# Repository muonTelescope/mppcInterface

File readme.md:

[headerIMG]

# MPPC Interface
Measuring and logging photon level light sources is a large part of high energy physics instrumentaiton. This board was created to power and collect data from eight MPPC (Multi Pixel photon counters) or SiPM (Silicon Photomultiplers). Provide coincidence logic and log the data out to a Raspberry Pi.

[img]

This is the main conntroller board of the muon telescope project. This board aimts to replace the current tools used

This is the technical manual for anyone wanting to modify, hack, remix, or program their own SiPM readout. The manual goes into fine detail about construction, assembly, and firmware which should encompass all basic knowledge.

## TOC

## Design
THe design was based off a combiniation of topologies from [sPhenix] design, our previous hardware iterations, and new needs in this version. The MPPCs need a very stable high voltage bias voltage that can be controled over this range in sub-milivolt steps. 

[topologyDiagarm]

This is done thoug hthe top high voltage being controalbe in 1V steps and is common across all eight chanels and a eight channel bottom DAC that provides a controlable virtual ground seperately for each channel.

The anode signal is then sent though a high amplification instrumentation amplifier and then sent to the FPGA's schmitt inputs. The conicidence logic is then done in the FPGA and its outputs are mapped to interupt vectors on the host machine.

### Components
Component selection was built off previous verisons, and the specific use case  of driving [Hamamtsu]'s MPPCs. The major ICs and other unique componets will be descibed below.

#### High Voltage Boost
*Maxim Semiconducr's* [MAX1932] has proven itself with proper layout in pervious interations of the design to provide a stable, controlable, low ripple high voltage for avalanche photodidoes. 

THe chip interanlly has a boost controller, current sensing for a current limit, and a 8b DAC that can be tied in to set the voltage over SPI.

#### Bottom DAC
The other half of the bias voltage is handled by the *Texas Instument* [DAC60508] 8 channel 12b (with a direct drop in replace for up to 16b) digital to analog converter. The linear regulation inside provides a stable output, and using the internal `2.5 V` precsion refrence LSB steps of `0.6 mV` are achived. THe output is highly linear and monotonic. 

The power consuption is also low at `0.6mA/ch` for future power constrained applicaitons.

### Schematic
### Layout
### Mechanics

## Firmware
### High Voltage
### Bottom DAC
### FPGA burning
### Compiling
### Flashing

## Gateware
### Pin connections
### Logic
### Compiling
### Flashing

## Setup
Download and flash a copy of the [Raspberry Pi OS](https://www.raspberrypi.com/software/) using either `dd` or the *Raspberry Pi imager* software.

### Raspberry Pi imager
Select the Raspberry Pi OS Lite and in advanced configuration menu (CTRL+SHIFT+X) enable ssh and add the WiFi credentials if the device will be connected over wireless network.

This video also shows using the software to flash a SD card [How to use Raspberry Pi Imager](https://www.youtube.com/watch?v=ntaXWS8Lk34)

### Advanced install with `dd`
Be very careful using `dd` to copy the image to the SD card. `dd` is a direct bit copy from the imput file to the output file and will indescriminately write over any drives without any checks or protection.

```bash
df -h
sudo umount sdx
sudo dd bs=4M if=<imgPath.img> of=/dev/sdx
```

Enable ssh by creating a blank `ssh` file in the root directory called *boot*.
```bash
cd boot
touch ssh
```

To setup connectingto WiFi on boot, a `/boot/wpa_supplicant.conf` file is created that is automatically copied over to `/etc/wpa_supplicant/wpa_supplicant.conf` on the next boot. 

```bash
nano /boot/wpa_supplicant.conf
```

And add in the relevant configuration.

```
ctrl_interface=DIR=/var/run/wpa_supplicant GROUP=netdev
country=<Insert 2 letter ISO 3166-1 country code here>
update_config=1

network={
 ssid="<Name of your wireless LAN>"
 psk="<Password for your wireless LAN>"
}
```

Insert the SD card into the Raspberry Pi, connect the ethernet cable (if connecting over wired network), and power (unless connecting though POE) and connect to the device using ssh.

You can figure out the IP address in several ways on linux you can use `nmap` or `arp` to search for the Raspberry Pi foundation's OUID (`DC:A6:32` for Raspberry Pi 4, `B8:27:EB` otherwise) on your local subnet. 

```bash
nmap -sP 192.168.1.0/24 | awk '/^Nmap/{ip=$NF}/B8:27:EB/{print ip}'
```

```bash
arp -na | grep -i b8:27:eb
```

For Windows
```cmd
arp -a | findstr b8-27-eb
```

It is also possible to ping a new install with the default hostname if DNS or the bonjour service has the device in its tables.

```bash
ping raspi
```

### Bootstrap
The setup script in the root directory can be run to set up a Raspberry pi from scratch. 

Connect to the raspberry pi using the IP adress found.
```bash
ssh pi@192.168.1.*
sudo apt install -y git
```

```bash
git clone https://github.com/muonTelescope/mppcInterface.git
cd mppcInterface
```

The root directory includes a setup script that updates the operationg system, sets up accounts, installs the toolchain, and enables all required modules. On cloning th repository on the Raspberry Pi, this file shoud be made executable and run.

```bash
chmod +x setup.sh
sudo ./setup.sh
```

expand filwsystem, not needed as pi does it on boot now.

Working buildsystem for gateware
```
Yosys 0.9+3981 (git sha1 7d2097b0, clang 7.0.1-8+rpi3+deb10u2 -fPIC -Os)
arachne-pnr 0.1+328+0 (git sha1 c40fb22, g++ 8.3.0-6+rpi1 -O2)

```

By default the spidev driver on raspberry pi has a maximum transfer size of 4096 bytes.
That might cause problems with this software so to change the default buffersize add spidev.bufsiz=65536 to /boot/cmdline.txt and reboot.
Where 65536 is the maximum size you want to allow.

get mac adress to set hostname
```bash
cat /sys/class/net/eth0/address | cut -d: -f4- | sed 's/://g' | tr [:lower:] [:upper:]
```

channelSelect.sh
```bash
#!/bin/bash

dtparam spi=off

gpio mode 6  out  # CS_DAC
gpio mode 23 out  # CS_MAX1932
gpio mode 5  out  # CS_FPGA

gpio write 6  1
gpio write 23 1
gpio write 5  1

sleep 2

gpio mode 12 out # MOSI
gpio mode 13 out # MISO
gpio mode 14 out # SCK

gpio write 12 $1
gpio write 13 $2
gpio write 14 $3

sleep 2
#rmmod spi_bcm2835
#modprobe spi_bcm2835

dtparam spi=on
```

softwareSerial read python
```python
import sys
import time
import difflib
import pigpio
import datetime
import binascii

RX=17

try:
        pi = pigpio.pi()
        pi.set_mode(RX, pigpio.INPUT)
        pi.bb_serial_read_open(RX, 115200, 8)

        print "DATA - SOFTWARE SERIAL:"
        while 1:
                (count, data) = pi.bb_serial_read(RX)
                if count:
			print str(datetime.datetime.now()) + " " +  str(binascii.hexlify(data))
                time.sleep(0.5)

except Exception as e:
	print(e)
        pi.bb_serial_read_close(RX)
        pi.stop()
```

A controller board for 

This is a continuation of a long process, over five years at this point. It is also part of a much broader set of tools and parts that make up the Muon Telesecope.

## Design

## Hardware
There are three main sections to the hardware. High voltage generation and control, Analog front end, and digital logic conatined in the FPGA.

### Bias Voltage
The MPPCs requre a bias of around 80V (varies greatly by model) with very low ripple and high precision. The gain of the sensors varies with respect to the voltage put across them and even a deviation of 10mV has a significat impact on the gain. The gain is also a function of ambient temperature and the bias needs to be controlabe to within a mV to adjust the gain as temperature changes.

[Gain vs Bias]
[Gain Vs temp chart]

The bias voltage is set though a top high voltage rail and a bottom DAC. This approach allows for a very high precision on the bottom dac along with the range on the top HV. With a 16b DAC, steps of under 100uV are possible, whcih is below the accuracy of most of the rest of the supply

For example to set the voltage to 78.434 the top rail is set to its minimal on voltage to ensure there is never a risk of a forward bias (although with the HV off the output is at 4.5V, the input voltage save the shotky didode drop so the risk is only there if the dac is ser to near its max voltage which may still be below the conduction voltage of the MPPC), then the bottom rail can be set to 1.566V, followed by the HV rail being set to 80V providing a voltage diffreential of 78.434 across the sensor.

#### HV Rail
The top high voltage rail is created using Maxim's [MAX1932] APD bias boost converter. This IC provides a low ripple 5V input to 55V to 110V output (design configurable to 20V-100V) with 8b digital control over SPI and built in current limiting set at 2.5mA.

Using a high amount of filtering on the inputs and outpurs, large bulk capacitors, a tight layout, EMC shields, and sectioned off ground and power planes, the output ripple as well as emitted noise is reduced significantly. The output ripple is well below 1mV.

The voltage range, and step size is dictated with setting R2, R3, and R4. The minimum and maximum voltage set using the equations for on page 7 of the datasheet, and there are 8 bits (256) intermediate values that are possible. The high switching portion was designed with general SMPS design requirements (short high current loops, separated ground planes, EMI shielding) providing a low ripple output (<5mVpp ripple) and no significant back EMF.

The Setting resistors are 0.01% and the chip provides a 0.5% accuracy which needs to be calibrated. The calibration and certification procedure is provided in another section of documention.

[Table of set R values and the range they create]
[Fucntion of byte to voltage with perfect resistors]

#### Bottom DAC

The "Bottom DAC" is the term used to describe the arrangement where the voltage supply at the anode of a reverse biased SiPM is used to "subtract" from the top bias voltage. It is implemented with a eight channel 16b [DAC80508] by Texas Instruments. This provides independent control with a 5V range for each of the eight chanels. 

### Analog Front End
The analog front end amplifier is also highly specilized. The design condierations to be considered are considerable and require specilized parts [MPPC AFE talk]. In the end the selection is a very high bandwidth low noise instrumentation amplifier with a 400x gain. The [OPA846] has a high slew rate of 625V/us and a gain bandwith product of 1.75Ghz providing a adequate bandwith of ~4.3Mhz with our gain. 

[Outfput waveform]

This provides waveforms from over xx photons to reach the 1.4V lower schmitt threadhold of the digital logic 3.3V/2-100mV. 

[Photn and gain calculation]
x photons needed * 40% efficency * 	1.7E6 * 1.602E-19C / nS?	

The aplifier's input in coupled with a DC blocking capacitor and routed very tightly on a single layer to reduce noise and emissions that will easily be amplified with such a high gain. The gain of 400x is acivhed with a 20k and 50R positive feedback in a non-inverting configuration. The output is AC coupled to make sure the output has minimal capacitive loading especially since we are only looking for a hihg speed signal output.

[Routing of AFE]

#### Digital Logic
The digital logic is done with a FPGA and can be reconfigured though gateware based on the detector configuration. The eight channels are connected to the GPIO and the schmitt inputs act as discriminators. The rest of the lines are run to three LEDs that can be used for indication and to the GPIO of the Raspberry Pi.

#### Power supply
The general supply rails are provide dby the host Raspberry pi connector. The entire board uses about 1W across all the modules. The 5V supply, after some back EMF filtering is provided to the HV supply as well as the AFE power module. The 3.3V is used on the FPGA and the signaling Power supply of the DAC.

Very stable +-5V rails are required for the analog front end to have have the low noise it needs. The Analog \pm 5V is seperated to its own power planes and is hevily filtered and decoupled ensuring very little noise that would show amplifed on the output. This supply is generated thougha commerical module which is rated at a low ripple and switching frequency.

A 1.2V linear regulator provides the core voltage to the FPGA.

#### Mounting
The hat is attached to the raspberry pi with four 2.6mm mounting holes form M2.5 screwas nad standoffs. A M2.5x11 standoff provides mounting and clearence. The size of the module is showin in the drawing below, it is the same sizing as a raspberry pi zero.

## Firmware
This repository contains firmware in the form of C++ libraries that can be linked into your own code as well as a basic data logging application that sets up everything and logs the counts to a file. 

#### High Voltage
The SPI bus is connected directly to the MAX1932. Chip select is active low and data is sent MSB (most significant bit first). Sending bytes to it sets the voltage. Setting them to 0x00 turns off the DC-DC converter portion. As values increase to 0xFF (256), the output voltage falls linearly.

```Arduino
//Example Arduino code that loops through all voltages.
//SCLK --> Pin 13 for Uno or Duemilanove
//DIN ---> Pin 11 for Uno or Duemilanove

#include <SPI.h>
#define CS 2 //Any pin

void setup(){
	Serial.begin(9600);
	pinMode(CS, OUTPUT);
	digitalWrite(CS, HIGH);
	SPI.begin();
	SPI.setBitOrder(MSBFIRST);
}

void loop(){
	for(int i = 0 ; i < 256 ; i++){
		digitalWrite(CS, LOW);
		SPI.transfer(i);
		digitalWrite(CS, HIGH);
		Serial.println(i);
	}
}
```

---
In the config file the voltage is set for 25*. 

#### DAC

## Gateware

#### Flashing

##### Clearing
##### Burning
##### File format

##### Compilation
###### Yosys
###### AracnePNR

## Absolute Maximum ratings
## Gaurenteed Ratings
## Manufacturing
### BOM
### PCB Assembly
The board has three fiducials and 1.152mm tooling holes for automated assembly.
### Artwork
### Labeling
## Safety
## Certifications
## Licence
## Attributions

- HV Calibration procedure and certification.

Glossary
MPPC Multi pixel photon counter, Hamamtsu Photonics's 
SiPM
DAC
Bias

# Old Version of docs

A single assembled board breaks out singals and provides all the interfaces that 4 [MPPC Sesnor](https://github.com/Sawaiz/mppcSensor) boards need. The power to each module is supplied via the [MPPC high voltage](https://github.com/Sawaiz/mppcHighVoltage) modules
attached board. It is able to be run independently for testing and debugging, or on a backplane with many others for more channels.

![][mppcInterfaceAssembly]

## Expansion Format

### SPI
The SPI exapansion format is designed to be infinetly expandable up to the signal propgation length and capactive loading. 

The Design of the SPI system is chained shift registers. The shift registers 

SPI EEPROM lies on each expansion board and has the code needed to interface with it (this sounds beautiful, really).
The EEPROM contains the device enumeration and drivers for all the 8 slots on its adress.
Master downloads drivers 

### I2C

## Hardware
The board attaches directly to a Raspberry Pi using the centered GPIO headers. The Raspberry Pi is mounted to the board via four standoffs. It is a stand alone board requiring no backplane. This board can be mounted via the M5 screw holes around the edge.

### Power
Power is supplied through two pins on the edge connector, or via the micro USB port on board. There is a 600mA buck regulator that provides power when the USB port is used. The board should be powered by 3.3V and a negative power supply module with convert it to -3.3V for the biasing for the op-amps.

### High Voltage
High voltage is supplied through a daughter board. Each channel has a independent voltage source that can be temperature modulated and monitored via the on board ADC. for more information about the modules, read [here](https://github.com/Sawaiz/mppcHighVoltage).

![][mppcInterfaceTopISO]

### Microcontroller
The side of the board has a Arduino compatible ([ATmega328](http://www.atmel.com/images/Atmel-8271-8-bit-AVR-Microcontroller-ATmega48A-48PA-88A-88PA-168A-168PA-328-328P_datasheet_Complete.pdf)) microcontroller, along with a USB part, USB to UART converter and other supporting circuitry. The button is connected to the reset pin. The programing port on board is a Tag-Connect 6 pin, and is only used for programing the Arduino bootloader.

![][mppcInterfaceBottom]

### I2C Switch
As all the ADC modules on the daughter boards have the same address, a 8 channel I2C switch ([TCA9548A](http://www.ti.com/lit/ds/symlink/tca9548a.pdf)) is used to communicate to them independently. The pins attached to it are referenced as master, as the microcontroller is acting as the master controlling it.

## BOM
The bill of materials is availible in [bom.csv](bom.csv) and is copied into a table below.

| Ref Des                                                                                          | Qty | Manufacturer          | MPN                 | Description                      |
| ------------------------------------------------------------------------------------------------ | ---:| --------------------- | ------------------- | -------------------------------- |
| C1                                                                                               | 1   | Wuerth Elektronik     | 885012105011        | CAP CER 0.22UF 10V X5R 0402      |
| C2                                                                                               | 1   | Wuerth Elektronik     | 885012208116        | CAP CER 0.047UF 100V X7R 1206    |
| C3 C5 C7 C9 C11 C13 C15 C17                                                                      | 8   | Wuerth Elektronik     | 885012205016        | CAP CER 0.047UF 10V X7R 0402     |
| C19                                                                                              | 1   | Samsung               | CL21B105KOFNNNG     | CAP CER 1UF 16V X7R 0805         |
| C20                                                                                              | 1   | Samsung               | CL31B105KCHNNNE     | CAP CER 1UF 100V X7R 1206        |
| C21                                                                                              | 1   | AVX                   | 22201C106MAT2A      | CAP CER 10UF 100V X7R 2220       |
| C22 C24                                                                                          | 2   | Murata                | GRM155C80J106ME11D  | CAP CER 10UF 6.3V X6S 0402       |
| C29 C28 C34 C33 C39 C38 C44 C43 C49 C48 C54 C53 C59 C58 C64 C63                                  | 16  | Wuerth Elektronik     | 885012105016        | CAP CER 0.1UF 16V X5R 0402       |
| C23 C32 C31 C27 C26 C37 C41 C42 C36 C4 C25 C6 C30 C8 C35 C10 C40 C12 C45 C14 C50 C16 C55 C18 C60 | 25  | Samsung               | CL05A105MP5NNNC     | CAP CER 1UF 10V X5R 0402         |
| C65                                                                                              | 1   | TDK                   | C1005X5R1A335M050BC | CAP CER 3.3UF 10V X5R 0402       |
| R1                                                                                               | 1   | Stackpole Electronics | RMCF0402FT1M13      | RES 1.13M OHM 1% 1/16W 0402      |
| R2                                                                                               | 1   | Stackpole Electronics | RMCF0402JT20R0      | RES 20 OHM 5% 1/16W 0402         |
| R3                                                                                               | 1   | Yageo                 | RT0402BRD072K49L    | RES SMD 2.49KOHM 0.1% 1/16W 0402 |
| R4                                                                                               | 1   | Yageo                 | RC0402FR-07806RL    | RES SMD 806 OHM 1% 1/16W 0402    |
| R5                                                                                               | 1   | Yageo                 | RT0402BRD07100KL    | RES SMD 100K OHM 0.1% 1/16W 0402 |
| R6                                                                                               | 1   | TE Connectivity       | CPF0402B23R7E1      | RES SMD 23.7 OHM 0.1% 1/16W 0402 |
| R7 R12 R17 R22 R27 R32 R37 R42                                                                   | 8   | Yageo                 | RT0402DRE071KL      | RES SMD 1K OHM 0.5% 1/16W 0402   |
| R8 R9 R13 R14 R18 R19 R23 R24 R28 R29 R33 R34 R38 R39 R43 R44                                    | 16  | Panasonic             | ERJ-2RKD49R9X       | RES SMD 49.9 OHM 0.5% 1/16W 0402 |
| R10 R15 R20 R25 R30 R35 R40 R45                                                                  | 8   | Stackpole Electronics | RNCF0402DTE20K0     | RES 20K OHM 0.5% 1/16W 0402      |
| R11                                                                                              | 1   | Stackpole Electronics | RMCF0402FT499K      | RES 499K OHM 1% 1/16W 0402       |
| D2                                                                                               | 1   | ON Semiconductor      | FDLL4148            | DIODE GEN PURP 100V 200MA LL34   |
| J1 J2 J3 J4 J5 J6 J7 J8                                                                          | 8   | Hirose                | U.FL-R-SMT-1(40)    | CONN U.FL RCPT STR 50 OHM SMD    |
| J9                                                                                               | 1   | Sullins               | SFH11-PBPC-D20-ST-BK| CONN HDR 40POS 0.1 GOLD PCB      |
| J10                                                                                              | 1   | FCI                   | 54601-906WPLF       | CONN MOD JACK 6P6C R/A UNSHLD    |
| J11                                                                                              | 1   | Harwin                | M20-8760542         | CONN HEADER SMD 10POS 2.54MM     |
| J12                                                                                              | 1   | FCI                   | 54602-908LF         | CONN MOD JACK 8P8C R/A UNSHLD    |
| L1                                                                                               | 1   | Bourns                | SRN4018-151M        | FIXED IND 150UH 320MA 2.4 OHM    |
| L2                                                                                               | 1   | Taiyo Yuden           | CBC3225T102KR       | FIXED IND 1MH 100MA 13 OHM SMD   |
| Q1                                                                                               | 1   | ON Semiconductor      | BSS123L             | MOSFET N-CH 100V 0.17A SOT-23    |
| U1                                                                                               | 1   | Texas Instruments     | DAC60508ZRTER       | IC DAC 12BIT V-OUT 16WQFN        |
| U2                                                                                               | 1   | Microchip             | MIC5504-1.2YM5-TR   | IC REG LINEAR 1.2V 300MA SOT23-5 |
| U3                                                                                               | 1   | Texas Instruments     | LM27761DSGR         | IC REG CHARGE PUMP ADJ 8WSON     |
| U4                                                                                               | 1   | Nexperia              | 74HC595PW-112       | IC 8BIT SHIFT REGISTER 16TSSOP   |
| U5                                                                                               | 1   | Maxim Integrated      | MAX1932ETC+T        | IC REG CTRLR FBR OPT 1OUT 12TQFN |
| U6 U7 U8 U9 U10 U11 U12 U13                                                                      | 8   | Texas Instruments     | OPA846IDBVT         | IC OPAMP VFB 1 CIRCUIT SOT23-5   |
| U14                                                                                              | 1   | Lattice Semiconductor | ICE40LP384-SG32     | IC FPGA 21 I/O 32QFN             |

Aslo availible though [octopart](https://octopart.com/bom-tool/T0iNvVYe) 

![][mppcInterfaceBottomISO]

## Software
The device acts as both a master and slave device. It takes instructions from an external I2C bus, and executes them on the AVR microcontroller to set voltages, provide telemetry, and preform closed loop control.

### AVR
The microcontroller on board takes commands sent to the whole module, and forwards them to each daughterboard. It primary control loop involves reading the temperature, finding the associated required bias voltage based on the temperature and setting the voltage on the high voltage supply, then checking if the output voltage is within specification of the required output, and fixing it if not. This loops for all eight channels. Otherwise there is an instruction queue of commands that come into the module.

### Module
The master can communicate to up to 128 slave devices the address is set within software. The master can request the temperature, or current voltage of any of the eight channels on board, select between different voltage to temperature curves, and set the bias voltage, or pulse the LED on the modules.

[mppcInterfaceAssembly]:  cad/renderings/mppcInterfaceAssembly.png  "View of Back of Board"
[mppcInterfaceTopISO]:    cad/renderings/mppcInterfaceTopISO.png    "Direct front view"
[mppcInterfaceBottomISO]: cad/renderings/mppcInterfaceBottomISO.png "Board rendering with EMI shield"
[mppcInterfaceBottom]:    cad/renderings/mppcInterfaceBottom.png    "Board rendering with EMI shield"

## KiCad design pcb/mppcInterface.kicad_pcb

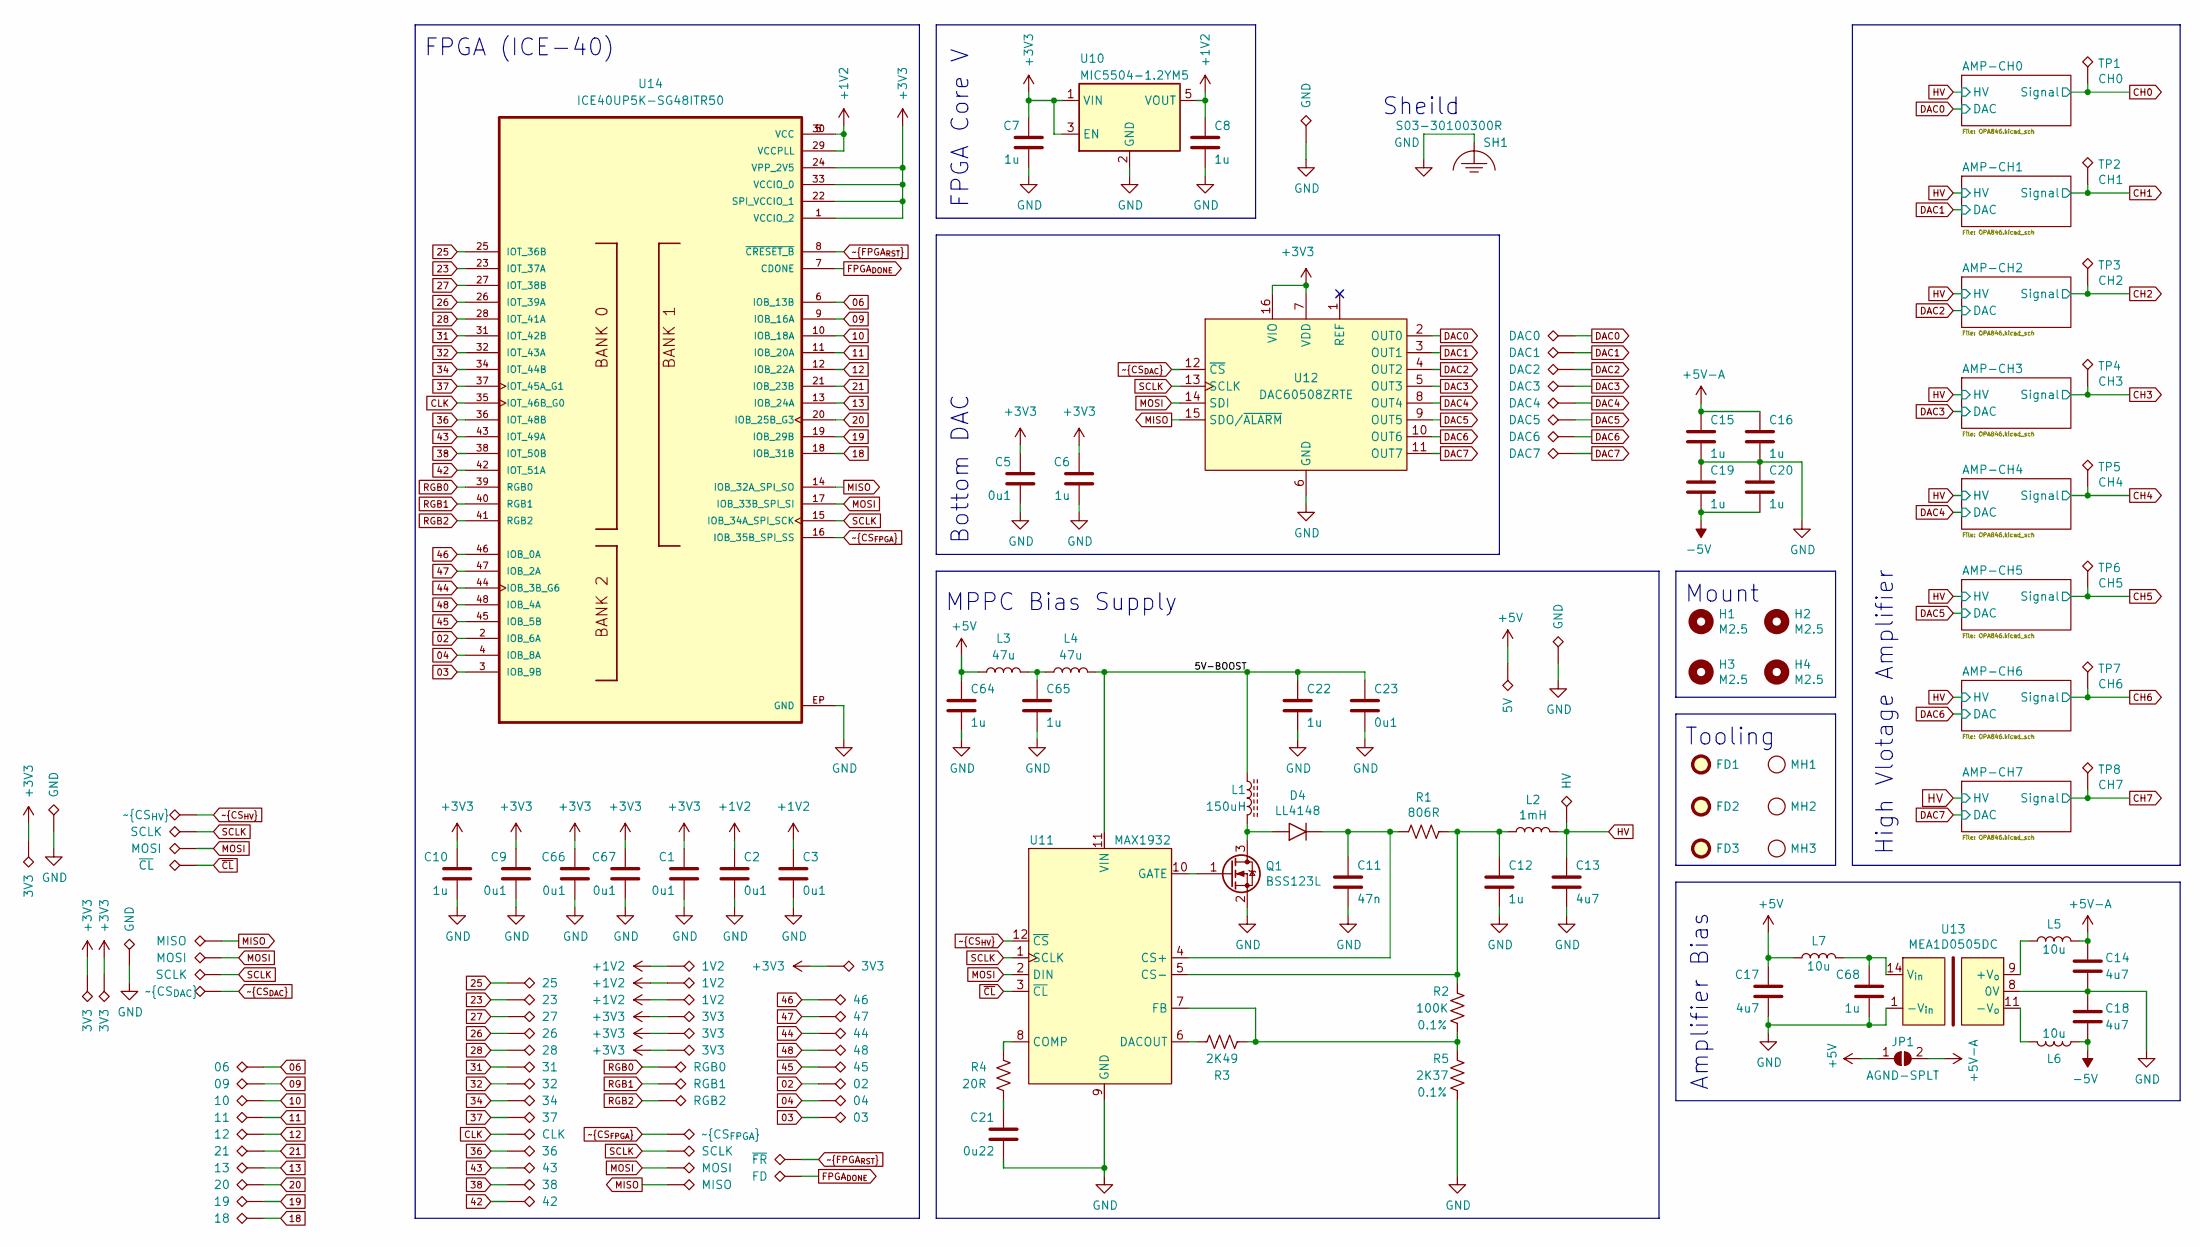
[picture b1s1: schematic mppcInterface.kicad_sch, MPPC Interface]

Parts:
C1, C2, C3, C5, C9, C23, C66, C67: 0u1; C-0402
C6, C7, C8, C10, C15, C16, C19, C20, C22: 1u; C-0402
C11: 47n; C-0805
C12: 1u; C-1206
C13: 4u7; C-2220
C14, C17, C18: 4u7; C-0805
C21: 0u22; C-0402
C64, C65, C68: 1u; C-0805
D4: LL4148; SOD-80
FD1, FD2, FD3: Fiducial; Fiducial_1.5mm_Mask3mm
H1, H2, H3, H4: M2.5; M2.5x11-Standoff
JP1: AGND-SPLT; SolderJumper-2_P1.3mm_Open_RoundedPad1.0x1.5mm
L1: 150uH; SRN4018
L2: 1mH; L-1210
L3, L4: 47u; L-0805
L5, L6, L7: 10u; L-0805
MH1, MH2, MH3: toolingHole; 1.152mm-ToolingHole
Q1: BSS123L; SOT-23-3
R1: 806R; R-0402
R2: 100K; R-0402; Tolerance 0.1%
R3: 2K49; R-0402
R4: 20R; R-0402
R5: 2K37; R-0402; Tolerance 0.1%
SH1: S03-30100300R
TP1: CH0; TestPoint_Pad_D1.0mm
TP2: CH1; TestPoint_Pad_D1.0mm
TP3: CH2; TestPoint_Pad_D1.0mm
TP4: CH3; TestPoint_Pad_D1.0mm
TP5: CH4; TestPoint_Pad_D1.0mm
TP6: CH5; TestPoint_Pad_D1.0mm
TP7: CH6; TestPoint_Pad_D1.0mm
TP8: CH7; TestPoint_Pad_D1.0mm
TP9: 5V; 0.1in Pin
TP11: 25; 0.1in Pin
TP12: 23; 0.1in Pin
TP13: 27; 0.1in Pin
TP14: 26; 0.1in Pin
TP15: 28; 0.1in Pin
TP16: 31; 0.1in Pin
TP17: 32; 0.1in Pin
TP18: 34; 0.1in Pin
TP19: 37; 0.1in Pin
TP20: CLK; 0.1in Pin
TP21: 36; 0.1in Pin
TP22: 43; 0.1in Pin
TP23: 38; 0.1in Pin
TP24: 42; 0.1in Pin
TP25, TP26, TP64: 1V2; 0.1in Pin
TP27, TP28, TP65, TP66, TP77, TP78, TP80: 3V3; 0.1in Pin
TP29: DAC3; 0.1in Pin
TP30: DAC2; 0.1in Pin
TP31: DAC1; 0.1in Pin
TP32: DAC0; 0.1in Pin
TP33: DAC4; 0.1in Pin
TP34: DAC5; 0.1in Pin
TP35: DAC6; 0.1in Pin
TP36: DAC7; 0.1in Pin
TP37: RGB0; 0.1in Pin
TP38: RGB1; 0.1in Pin
TP39: RGB2; 0.1in Pin
TP40: 46; 0.1in Pin
TP41: 47; 0.1in Pin
TP42: 44; 0.1in Pin
TP43: 48; 0.1in Pin
TP44: 45; 0.1in Pin
TP45: 02; 0.1in Pin
TP46: 04; 0.1in Pin
TP47: 03; 0.1in Pin
TP48: ~{CS_{FPGA}}; 0.1in Pin
TP49, TP70, TP73: SCLK; 0.1in Pin
TP50, TP69, TP74: MOSI; 0.1in Pin
TP51, TP68: MISO; 0.1in Pin
TP52: 06; 0.1in Pin
TP53: 09; 0.1in Pin
TP54: 10; 0.1in Pin
TP55: 11; 0.1in Pin
TP56: 12; 0.1in Pin
TP57: 21; 0.1in Pin
TP58: 13; 0.1in Pin
TP59: 20; 0.1in Pin
TP60: 19; 0.1in Pin
TP61: 18; 0.1in Pin
TP62: ~{FR}; 0.1in Pin
TP63: FD; 0.1in Pin
TP67, TP76, TP79, TP81: GND; 0.1in Pin
TP71: ~{CS_{DAC}}; 0.1in Pin
TP72: ~{CS_{HV}}; 0.1in Pin
TP75: ~{CL}; 0.1in Pin
TP82: HV; 0.1in Pin
U10: MIC5504-1.2YM5; SOT-23-5
U11: MAX1932; TQFN-12
U12: DAC60508ZRTE; DAC80508-RTE
U13: MEA1D0505DC; MEA1-D
U14: ICE40UP5K-SG48ITR50; ICE40-UP5K-SG48I; PARTREV 1.4

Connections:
02: TP45.1, U14.2 (IOB_6A)
03: TP47.1, U14.3 (IOB_9B)
04: TP46.1, U14.4 (IOB_8A)
06: TP52.1, U14.6 (IOB_13B)
09: TP53.1, U14.9 (IOB_16A)
10: TP54.1, U14.10 (IOB_18A)
11: TP55.1, U14.11 (IOB_20A)
12: TP56.1, U14.12 (IOB_22A)
13: TP58.1, U14.13 (IOB_24A)
18: TP61.1, U14.18 (IOB_31B)
19: TP60.1, U14.19 (IOB_29B)
20: TP59.1, U14.20 (IOB_25B_G3)
21: TP57.1, U14.21 (IOB_23B)
23: TP12.1, U14.23 (IOT_37A)
25: TP11.1, U14.25 (IOT_36B)
26: TP14.1, U14.26 (IOT_39A)
27: TP13.1, U14.27 (IOT_38B)
28: TP15.1, U14.28 (IOT_41A)
31: TP16.1, U14.31 (IOT_42B)
32: TP17.1, U14.32 (IOT_43A)
34: TP18.1, U14.34 (IOT_44B)
36: TP21.1, U14.36 (IOT_48B)
37: TP19.1, U14.37 (IOT_45A_G1)
38: TP23.1, U14.38 (IOT_50B)
42: TP24.1, U14.42 (IOT_51A)
43: TP22.1, U14.43 (IOT_49A)
44: TP42.1, U14.44 (IOB_3B_G6)
45: TP44.1, U14.45 (IOB_5B)
46: TP40.1, U14.46 (IOB_0A)
47: TP41.1, U14.47 (IOB_2A)
48: TP43.1, U14.48 (IOB_4A)
+1V2: C2.2, C3.2, C8.2, TP25.1, TP26.1, TP64.1, U10.5 (VOUT), U14.5 (VCC), U14.29 (VCCPLL), U14.30 (VCC)
+3V3: C1.2, C5.2, C6.2, C7.2, C9.2, C10.2, C66.2, C67.2, TP27.1, TP28.1, TP65.1, TP66.1, TP77.1, TP78.1, TP80.1, U10.1 (VIN), U10.3 (EN), U12.7 (VDD), U12.16 (VIO), U14.1 (VCCIO_2), U14.22 (SPI_VCCIO_1), U14.24 (VPP_2V5), U14.33 (VCCIO_0)
+5V: C17.1, C64.2, JP1.1 (A), L3.1, L7.1, TP9.1
+5V-A: C14.1, C15.2, C16.2, JP1.2 (B), L5.2; also elsewhere on the board
-5V: C18.2, C19.1, C20.1, L6.1; also elsewhere on the board
/5V-BOOST: C22.2, C23.1, L1.1, L4.2, U11.11 (VIN)
CH0: TP1.1; also elsewhere on the board
CH1: TP2.1; also elsewhere on the board
CH2: TP3.1; also elsewhere on the board
CH3: TP4.1; also elsewhere on the board
CH4: TP5.1; also elsewhere on the board
CH5: TP6.1; also elsewhere on the board
CH6: TP7.1; also elsewhere on the board
CH7: TP8.1; also elsewhere on the board
CLK: TP20.1, U14.35 (IOT_46B_G0)
DAC0: TP32.1, U12.2 (OUT0); also elsewhere on the board
DAC1: TP31.1, U12.3 (OUT1); also elsewhere on the board
DAC2: TP30.1, U12.4 (OUT2); also elsewhere on the board
DAC3: TP29.1, U12.5 (OUT3); also elsewhere on the board
DAC4: TP33.1, U12.8 (OUT4); also elsewhere on the board
DAC5: TP34.1, U12.9 (OUT5); also elsewhere on the board
DAC6: TP35.1, U12.10 (OUT6); also elsewhere on the board
DAC7: TP36.1, U12.11 (OUT7); also elsewhere on the board
FPGA_{DONE}: TP63.1, U14.7 (CDONE)
GND: C1.1, C2.1, C3.1, C5.1, C6.1, C7.1, C8.1, C9.1, C10.1, C11.2, C12.2, C13.2, C14.2, C15.1, C16.1, C17.2, C18.1, C19.2, C20.2, C21.2, C22.1, C23.2, C64.1, C65.1, C66.1, C67.1, C68.2, Q1.2 (S), R5.2, SH1.1 (SHIELD), TP67.1, TP76.1, TP79.1, TP81.1, U10.2 (GND), U11.9 (GND), U12.6 (GND), U13.1 (-V_{in}), U13.8 (0V), U14.EP (GND); also elsewhere on the board
HV: C13.1, L2.2, TP82.1; also elsewhere on the board
MISO: TP51.1, TP68.1, U12.15 (SDO/~ALARM), U14.14 (IOB_32A_SPI_SO)
MOSI: TP50.1, TP69.1, TP74.1, U11.2 (DIN), U12.14 (SDI), U14.17 (IOB_33B_SPI_SI)
unnamed: C21.1, R4.2
unnamed: C65.2, L3.2, L4.1
unnamed 69: D4.2 (A), L1.2, Q1.3 (D); also elsewhere on the board
unnamed 70: C11.1, D4.1 (K), R1.2, U11.4 (CS+); also elsewhere on the board
unnamed: Q1.1 (G), U11.10 (GATE)
unnamed: R4.1, U11.8 (COMP)
unnamed: C12.1, L2.1, R1.1, R2.1, U11.5 (CS-)
unnamed: R3.2, U11.6 (DACOUT)
unnamed: R2.2, R3.1, R5.1, U11.7 (FB)
unnamed: L5.1, U13.9 (+V_{o})
unnamed: L6.2, U13.11 (-V_{o})
unnamed: C68.1, L7.2, U13.14 (V_{in})
RGB0: TP37.1, U14.39 (RGB0)
RGB1: TP38.1, U14.40 (RGB1)
RGB2: TP39.1, U14.41 (RGB2)
SCLK: TP49.1, TP70.1, TP73.1, U11.1 (SCLK), U12.13 (SCLK), U14.15 (IOB_34A_SPI_SCK)
~CL: TP75.1, U11.3 (~CL)
~CS_{DAC}: TP71.1, U12.12 (~CS)
~CS_{FPGA}: TP48.1, U14.16 (IOB_35B_SPI_SS)
~CS_{HV}: TP72.1, U11.12 (~CS)
~FPGA_{RST}: TP62.1, U14.8 (~CRESET_B)

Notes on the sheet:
MPPC Bias Supply
Sheild
FPGA Core V
High Vlotage Amplifier
FPGA (ICE-40)
Tooling
Mount
Bottom DAC
Amplifier Bias

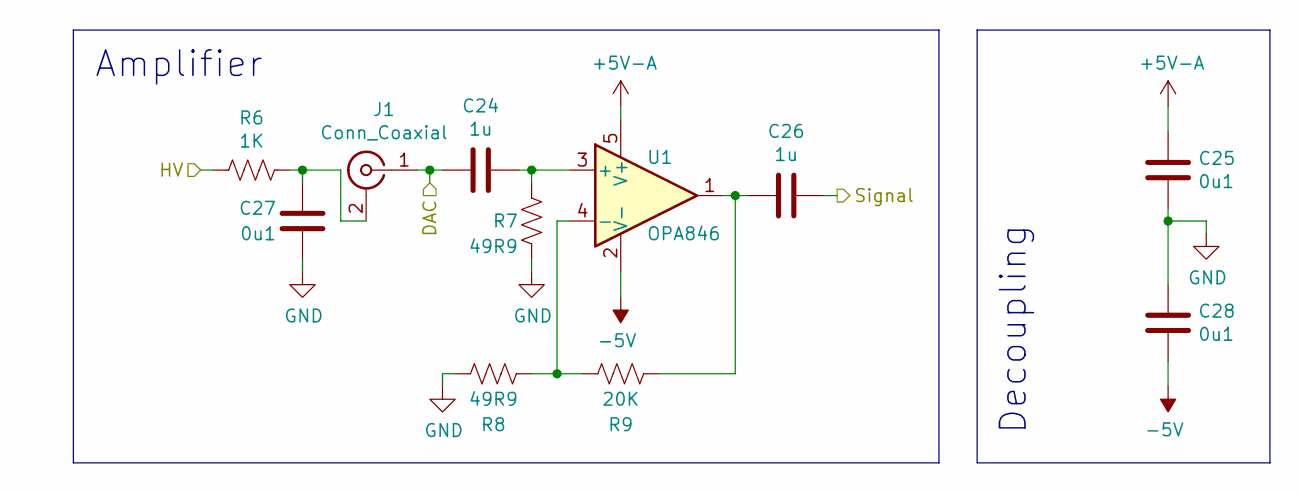
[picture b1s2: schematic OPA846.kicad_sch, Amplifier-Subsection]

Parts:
C24, C26: 1u; C-0402
C25, C27, C28: 0u1; C-0402
J1: Conn_Coaxial; U.FL
R6: 1K; R-0402
R7, R8: 49R9; R-0402
R9: 20K; R-0402
U1: OPA846; SOT-23-5

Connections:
+5V-A: C25.1, U1.5 (V+); also elsewhere on the board
-5V: C28.2, U1.2 (V-); also elsewhere on the board
CH0: C26.1; also elsewhere on the board
DAC0: C24.2, J1.1 (In); also elsewhere on the board
GND: C25.2, C27.2, C28.1, R7.1, R8.1; also elsewhere on the board
HV: R6.2; also elsewhere on the board
unnamed: C26.2, R9.1, U1.1
unnamed: C27.1, J1.2 (Ext), R6.1
unnamed: C24.1, R7.2, U1.3 (+)
unnamed: R8.2, R9.2, U1.4 (-)

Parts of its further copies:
C29, C31, C34, C36, C39, C41, C44, C46, C49, C51, C54, C56, C59, C61: 1u; C-0402
C30, C32, C33, C35, C37, C38, C40, C42, C43, C45, C47, C48, C50, C52, C53, C55, C57, C58, C60, C62, C63: 0u1; C-0402
J2, J3, J4, J5, J6, J7, J8: Conn_Coaxial; U.FL
R10, R14, R18, R22, R26, R30, R34: 1K; R-0402
R11, R12, R15, R16, R19, R20, R23, R24, R27, R28, R31, R32, R35, R36: 49R9; R-0402
R13, R17, R21, R25, R29, R33, R37: 20K; R-0402
U2, U3, U4, U5, U6, U7, U8: OPA846; SOT-23-5

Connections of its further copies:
+5V-A: C30.1, C35.1, C40.1, C45.1, C50.1, C55.1, C60.1, U2.5 (V+), U3.5 (V+), U4.5 (V+), U5.5 (V+), U6.5 (V+), U7.5 (V+), U8.5 (V+); also elsewhere on the board
-5V: C33.2, C38.2, C43.2, C48.2, C53.2, C58.2, C63.2, U2.2 (V-), U3.2 (V-), U4.2 (V-), U5.2 (V-), U6.2 (V-), U7.2 (V-), U8.2 (V-); also elsewhere on the board
CH1: C31.1; also elsewhere on the board
CH2: C36.1; also elsewhere on the board
CH3: C41.1; also elsewhere on the board
CH4: C46.1; also elsewhere on the board
CH5: C51.1; also elsewhere on the board
CH6: C56.1; also elsewhere on the board
CH7: C61.1; also elsewhere on the board
DAC1: C29.2, J2.1 (In); also elsewhere on the board
DAC2: C34.2, J3.1 (In); also elsewhere on the board
DAC3: C39.2, J4.1 (In); also elsewhere on the board
DAC4: C44.2, J5.1 (In); also elsewhere on the board
DAC5: C49.2, J6.1 (In); also elsewhere on the board
DAC6: C54.2, J7.1 (In); also elsewhere on the board
DAC7: C59.2, J8.1 (In); also elsewhere on the board
GND: C30.2, C32.2, C33.1, C35.2, C37.2, C38.1, C40.2, C42.2, C43.1, C45.2, C47.2, C48.1, C50.2, C52.2, C53.1, C55.2, C57.2, C58.1, C60.2, C62.2, C63.1, R11.1, R12.1, R15.1, R16.1, R19.1, R20.1, R23.1, R24.1, R27.1, R28.1, R31.1, R32.1, R35.1, R36.1; also elsewhere on the board
HV: R10.2, R14.2, R18.2, R22.2, R26.2, R30.2, R34.2; also elsewhere on the board
unnamed: C31.2, R13.1, U2.1
unnamed: C36.2, R17.1, U3.1
unnamed: C41.2, R21.1, U4.1
unnamed: C46.2, R25.1, U5.1
unnamed: C51.2, R29.1, U6.1
unnamed: C56.2, R33.1, U7.1
unnamed: C61.2, R37.1, U8.1
unnamed: C32.1, J2.2 (Ext), R10.1
unnamed: C37.1, J3.2 (Ext), R14.1
unnamed: C42.1, J4.2 (Ext), R18.1
unnamed: C47.1, J5.2 (Ext), R22.1
unnamed: C52.1, J6.2 (Ext), R26.1
unnamed: C57.1, J7.2 (Ext), R30.1
unnamed: C62.1, J8.2 (Ext), R34.1
unnamed: C29.1, R11.2, U2.3 (+)
unnamed: R12.2, R13.2, U2.4 (-)
unnamed: C34.1, R15.2, U3.3 (+)
unnamed: R16.2, R17.2, U3.4 (-)
unnamed: C39.1, R19.2, U4.3 (+)
unnamed: R20.2, R21.2, U4.4 (-)
unnamed: C44.1, R23.2, U5.3 (+)
unnamed: R24.2, R25.2, U5.4 (-)
unnamed: C49.1, R27.2, U6.3 (+)
unnamed: R28.2, R29.2, U6.4 (-)
unnamed: C54.1, R31.2, U7.3 (+)
unnamed: R32.2, R33.2, U7.4 (-)
unnamed: C59.1, R35.2, U8.3 (+)
unnamed: R36.2, R37.2, U8.4 (-)

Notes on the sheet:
Amplifier
Decoupling

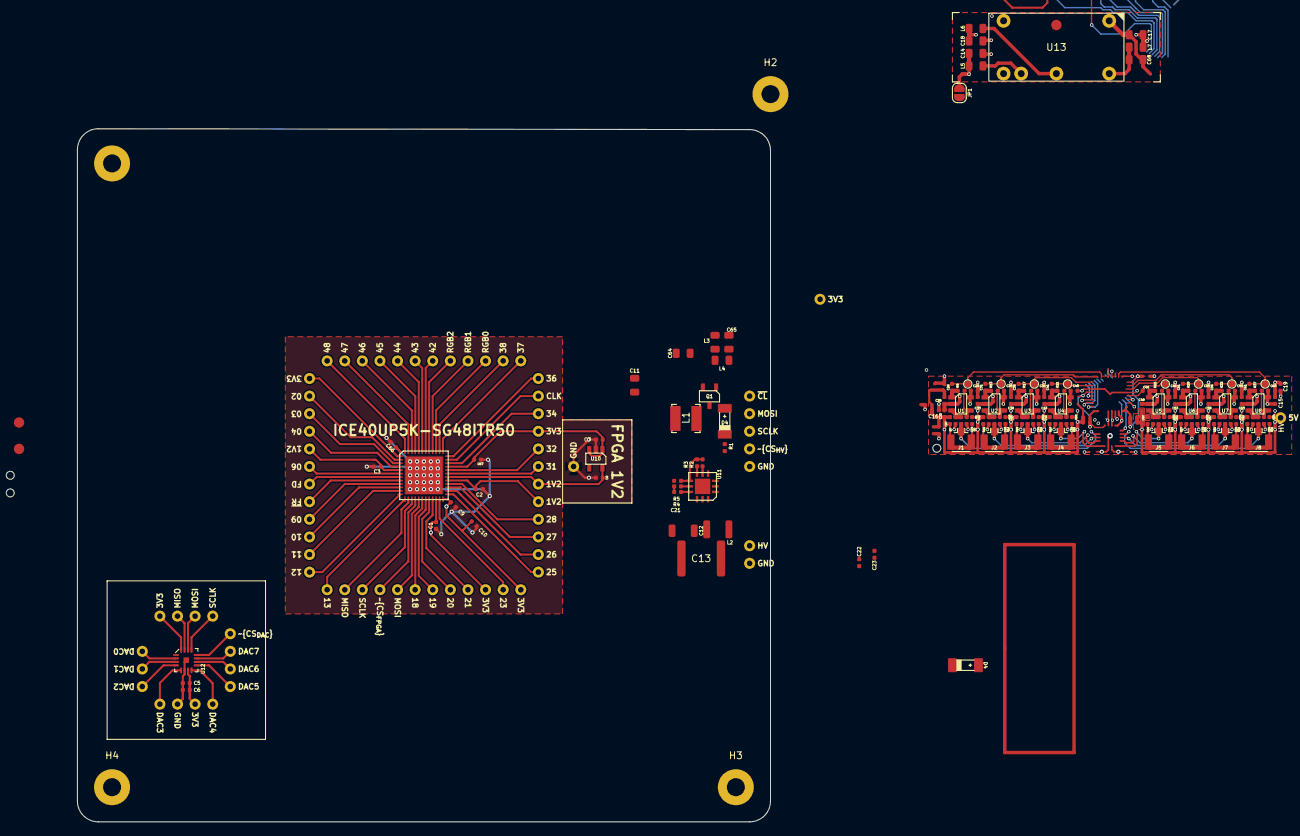
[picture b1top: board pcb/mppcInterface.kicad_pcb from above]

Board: 2 copper layers, 100.0 x 100.0 mm, 228 parts (1 on the bottom side), 112 nets.

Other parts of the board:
D4#2: LL4148; SOD-80

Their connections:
unnamed 69: D4#2.2 (A); also elsewhere on the board
unnamed 70: D4#2.1 (K); also elsewhere on the board

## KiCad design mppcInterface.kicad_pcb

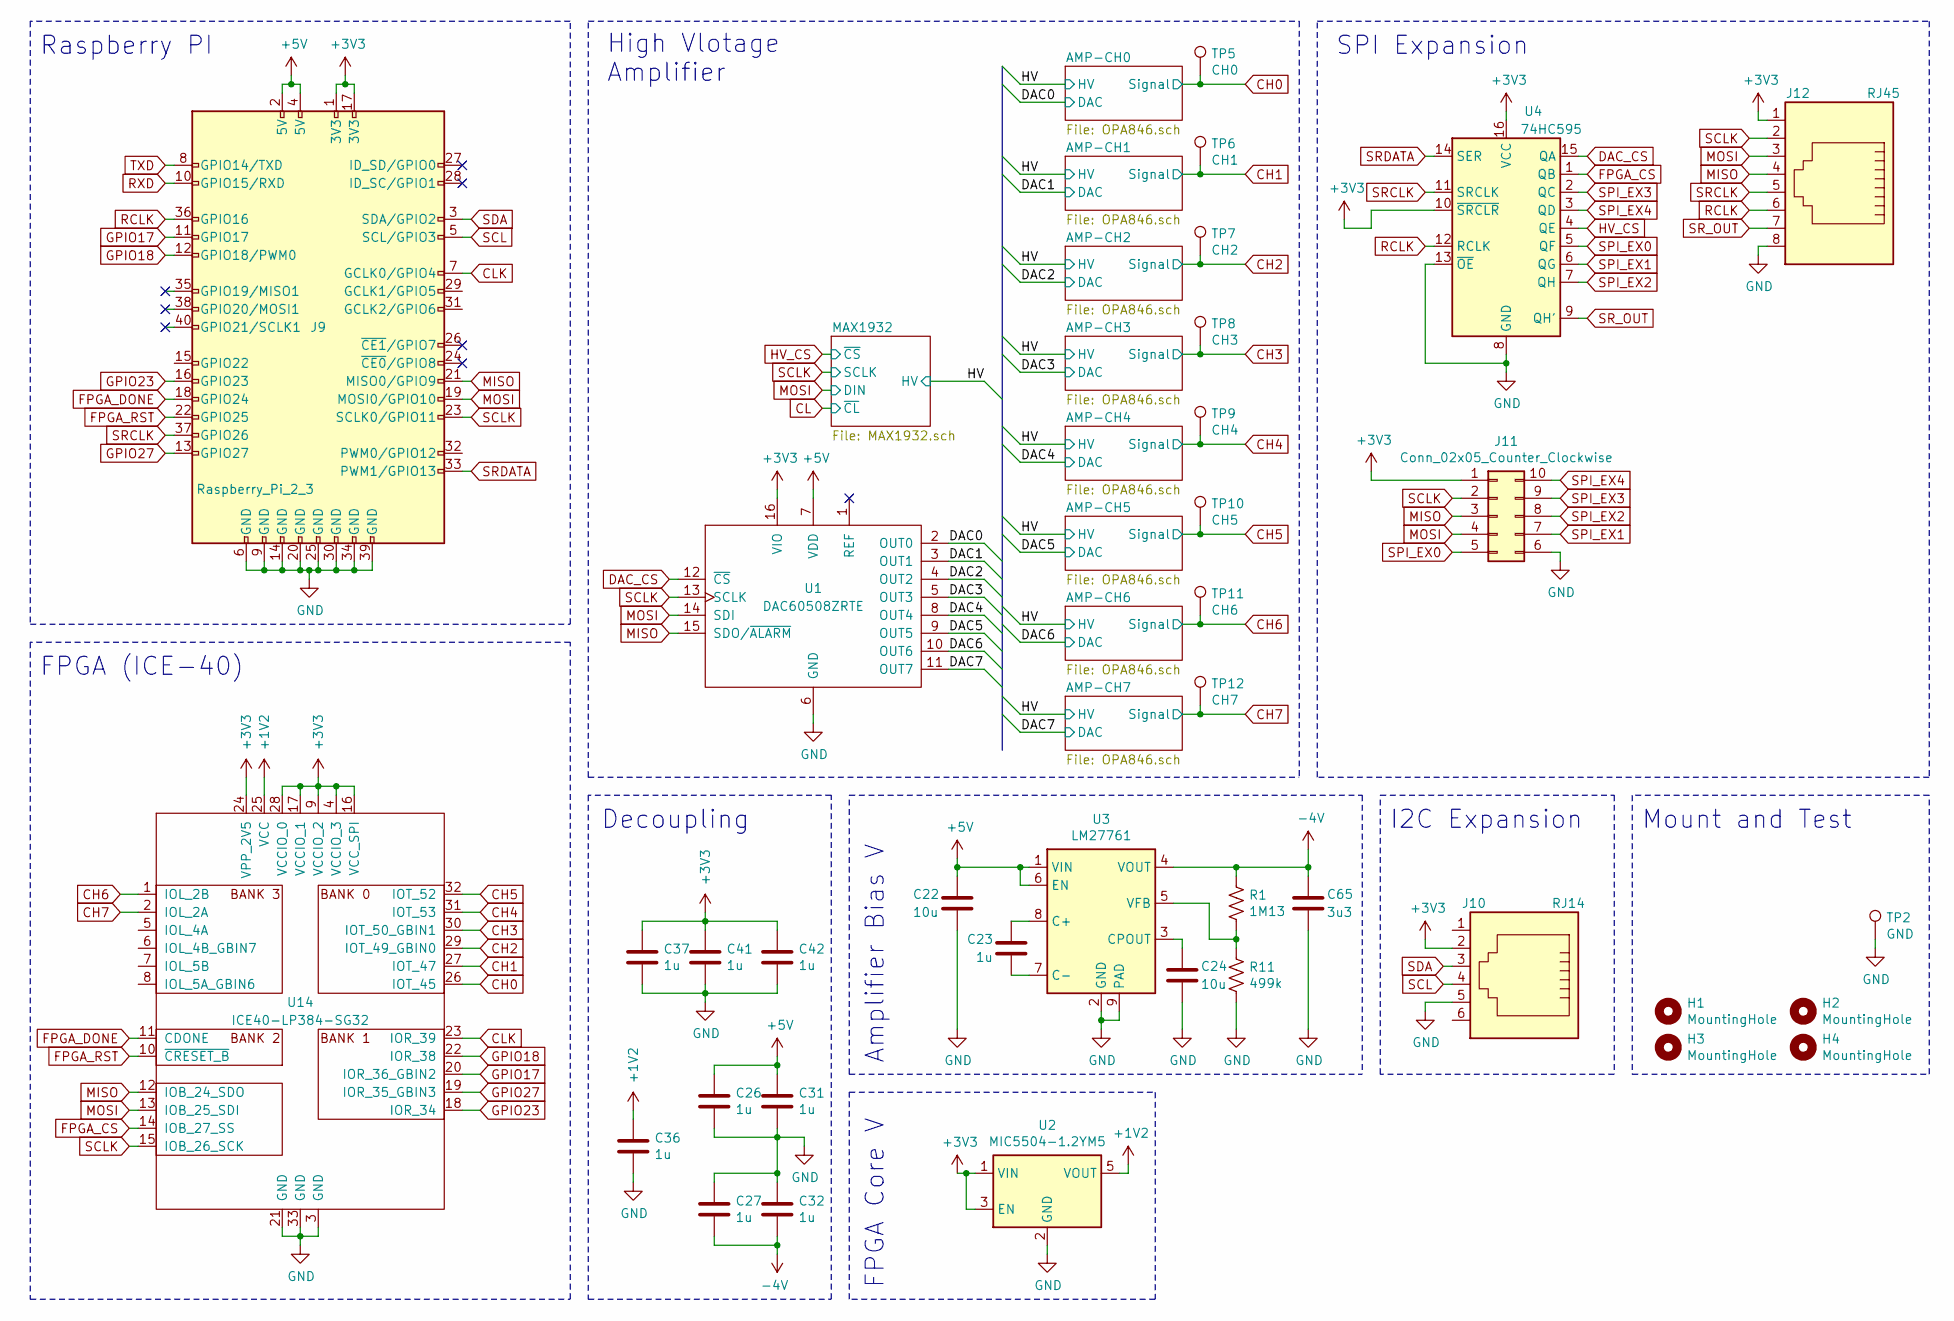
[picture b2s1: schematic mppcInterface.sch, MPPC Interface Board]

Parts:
C22, C24: 10u; C_0402_1005Metric
C23, C26, C27, C31, C32, C36, C37, C41, C42: 1u; C_0402_1005Metric
C65: 3u3; C_0402_1005Metric
H1, H2, H3, H4: MountingHole; MountingHole_2.7mm_M2.5_DIN965
J9: Raspberry_Pi_2_3; PinSocket_2x20_P2.54mm_Vertical
J10: RJ14; RJ12_Amphenol_54601
J11: Conn_02x05_Counter_Clockwise; PinHeader_2x05_P2.54mm_Vertical_SMD
J12: RJ45; RJ45_Amphenol_54602-x08_Horizontal
R1: 1M13; R_0402_1005Metric
R11: 499k; R_0402_1005Metric
TP2: GND; TestPoint_Bridge_Pitch2.0mm_Drill0.7mm
TP5: CH0; TestPoint_Bridge_Pitch2.0mm_Drill0.7mm
TP6: CH1; TestPoint_Bridge_Pitch2.0mm_Drill0.7mm
TP7: CH2; TestPoint_Bridge_Pitch2.0mm_Drill0.7mm
TP8: CH3; TestPoint_Bridge_Pitch2.0mm_Drill0.7mm
TP9: CH4; TestPoint_Bridge_Pitch2.0mm_Drill0.7mm
TP10: CH5; TestPoint_Bridge_Pitch2.0mm_Drill0.7mm
TP11: CH6; TestPoint_Bridge_Pitch2.0mm_Drill0.7mm
TP12: CH7; TestPoint_Bridge_Pitch2.0mm_Drill0.7mm
U1: DAC60508ZRTE; QFN-16-1EP_3x3mm_P0.5mm_EP1.8x1.8mm
U2: MIC5504-1.2YM5; SOT-23-5
U3: LM27761; WSON-8-1EP_2x2mm_P0.5mm_EP0.9x1.6mm
U4: 74HC595; TSSOP-16_4.4x5mm_P0.65mm
U14: ICE40-LP384-SG32; QFN-32-1EP_5x5mm_P0.5mm_EP3.45x3.45mm

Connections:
+1V2: C36.2, U2.5 (VOUT), U14.25 (VCC)
+3V3: C37.2, C41.2, C42.2, J9.1 (3V3), J9.17 (3V3), J10.2, J11.1, J12.1, U1.16 (VIO), U2.1 (VIN), U2.3 (EN), U4.10 (~SRCLR), U4.16 (VCC), U14.4 (VCCIO_3), U14.9 (VCCIO_2), U14.16 (VCC_SPI), U14.17 (VCCIO_1), U14.24 (VPP_2V5), U14.28 (VCCIO_0)
+5V: C22.1, C26.2, C31.1, J9.2 (5V), J9.4 (5V), U1.7 (VDD), U3.1 (VIN), U3.6 (EN); also elsewhere on the board
-4V: C27.1, C32.2, C65.1, R1.1, U3.4 (VOUT); also elsewhere on the board
/DAC0: U1.2 (OUT0); also elsewhere on the board
/DAC1: U1.3 (OUT1); also elsewhere on the board
/DAC2: U1.4 (OUT2); also elsewhere on the board
/DAC3: U1.5 (OUT3); also elsewhere on the board
/DAC4: U1.8 (OUT4); also elsewhere on the board
/DAC5: U1.9 (OUT5); also elsewhere on the board
/DAC6: U1.10 (OUT6); also elsewhere on the board
/DAC7: U1.11 (OUT7); also elsewhere on the board
CH0: TP5.1, U14.26 (IOT_45); also elsewhere on the board
CH1: TP6.1, U14.27 (IOT_47); also elsewhere on the board
CH2: TP7.1, U14.29 (IOT_49_GBIN0); also elsewhere on the board
CH3: TP8.1, U14.30 (IOT_50_GBIN1); also elsewhere on the board
CH4: TP9.1, U14.31 (IOT_53); also elsewhere on the board
CH5: TP10.1, U14.32 (IOT_52); also elsewhere on the board
CH6: TP11.1, U14.1 (IOL_2B); also elsewhere on the board
CH7: TP12.1, U14.2 (IOL_2A); also elsewhere on the board
CLK: J9.7 (GCLK0/GPIO4), U14.23 (IOR_39)
DAC_CS: U1.12 (~CS), U4.15 (QA)
FPGA_CS: U4.1 (QB), U14.14 (IOB_27_SS)
FPGA_DONE: J9.18 (GPIO24), U14.11 (CDONE)
FPGA_RST: J9.22 (GPIO25), U14.10 (~CRESET_B)
GND: C22.2, C24.2, C26.1, C27.2, C31.2, C32.1, C36.1, C37.1, C41.1, C42.1, C65.2, J9.6 (GND), J9.9 (GND), J9.14 (GND), J9.20 (GND), J9.25 (GND), J9.30 (GND), J9.34 (GND), J9.39 (GND), J10.5, J11.6, J12.8, R11.2, TP2.1, U1.6 (GND), U2.2 (GND), U3.2 (GND), U3.9 (PAD), U4.8 (GND), U4.13 (~OE), U14.3 (GND), U14.21 (GND), U14.33 (GND); also elsewhere on the board
GPIO17: J9.11 (GPIO17), U14.20 (IOR_36_GBIN2)
GPIO18: J9.12 (GPIO18/PWM0), U14.22 (IOR_38)
GPIO23: J9.16 (GPIO23), U14.18 (IOR_34)
GPIO27: J9.13 (GPIO27), U14.19 (IOR_35_GBIN3)
HV_CS: U4.4 (QE); also elsewhere on the board
MISO: J9.21 (MISO0/GPIO9), J11.3, J12.4, U1.15 (SDO/~ALARM), U14.12 (IOB_24_SDO)
MOSI: J9.19 (MOSI0/GPIO10), J11.4, J12.3, U1.14 (SDI), U14.13 (IOB_25_SDI); also elsewhere on the board
unnamed: C23.1, U3.8 (C+)
unnamed: C23.2, U3.7 (C-)
unnamed: C24.1, U3.3 (CPOUT)
unnamed: R1.2, R11.1, U3.5 (VFB)
RCLK: J9.36 (GPIO16), J12.6, U4.12 (RCLK)
RXD: J9.10 (GPIO15/RXD)
SCL: J9.5 (SCL/GPIO3), J10.4
SCLK: J9.23 (SCLK0/GPIO11), J11.2, J12.2, U1.13 (SCLK), U14.15 (IOB_26_SCK); also elsewhere on the board
SDA: J9.3 (SDA/GPIO2), J10.3
SPI_EX0: J11.5, U4.5 (QF)
SPI_EX1: J11.7, U4.6 (QG)
SPI_EX2: J11.8, U4.7 (QH)
SPI_EX3: J11.9, U4.2 (QC)
SPI_EX4: J11.10, U4.3 (QD)
SRCLK: J9.37 (GPIO26), J12.5, U4.11 (SRCLK)
SRDATA: J9.33 (PWM1/GPIO13), U4.14 (SER)
SR_OUT: J12.7, U4.9 (QH')
TXD: J9.8 (GPIO14/TXD)

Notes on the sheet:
I2C Expansion
Mount and Test
SPI Expansion
High Vlotage Amplifier
Amplifier Bias V
FPGA Core V
Raspberry PI
FPGA (ICE-40)
Decoupling

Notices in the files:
pcb/mppcInterface.kicad_pcb:
CERN-OHL-2.0
